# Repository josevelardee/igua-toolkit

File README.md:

# The IGUA toolkit
This is the igua toolkit : )
An open source project to help us get reliable water for everyone, everywhere, anytime.
Done with he support from:

# igua agua, utec ventures, startup perú

#hola!

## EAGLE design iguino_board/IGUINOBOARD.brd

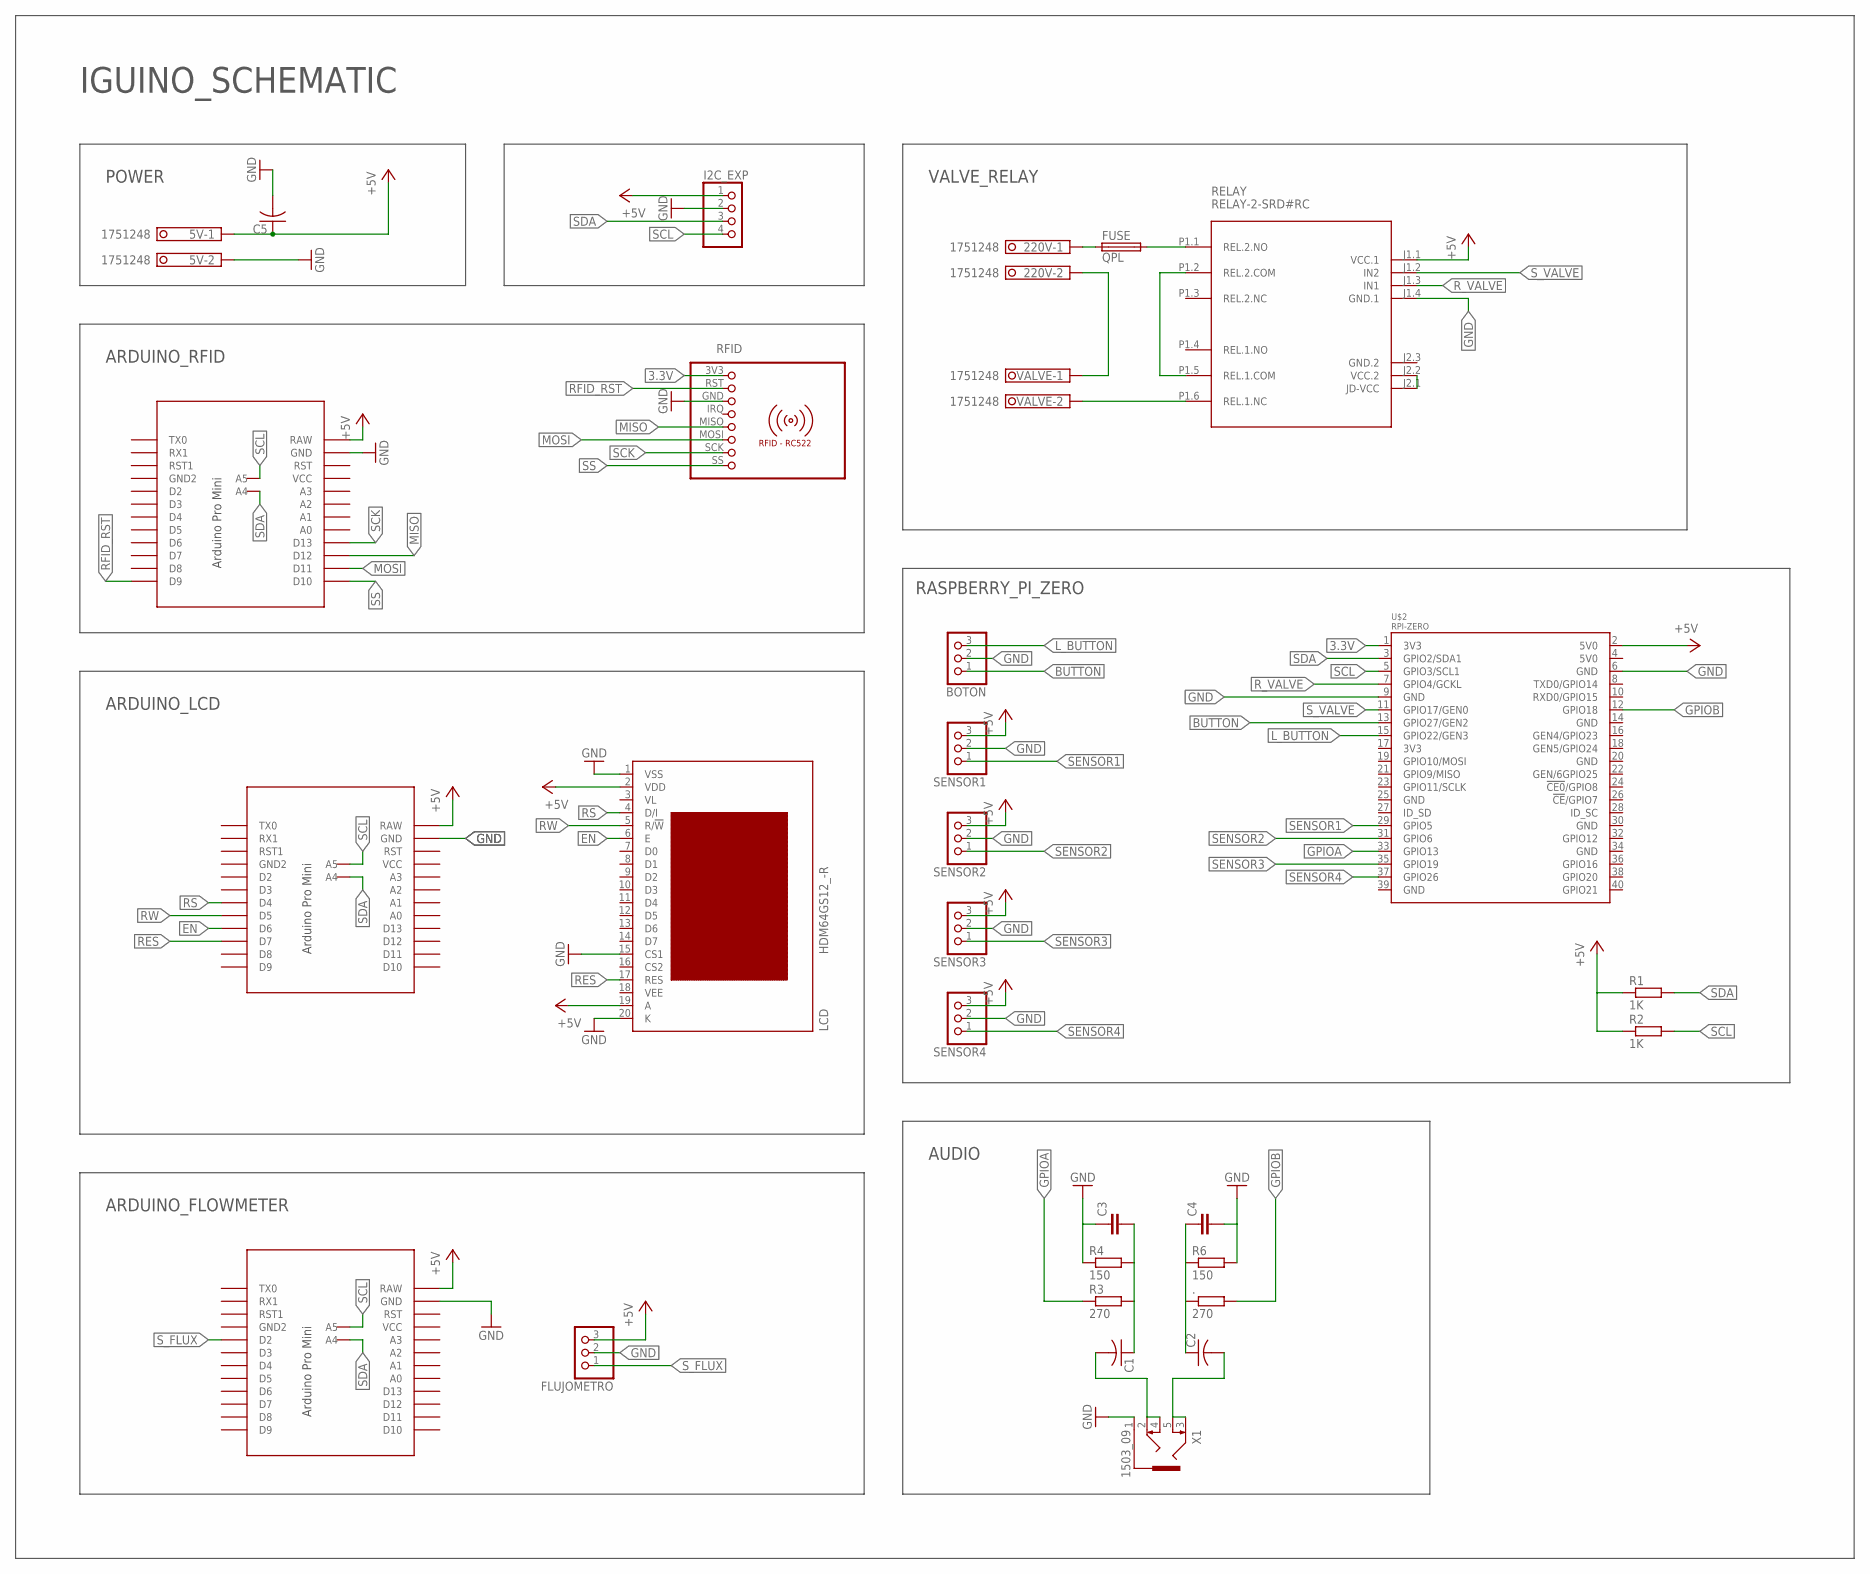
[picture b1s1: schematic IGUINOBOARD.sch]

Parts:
5V, 220V: 1751248
.: 270; 0204/7
BOTON: PINHD-1X3; 1X03
C1, C2, C5: C-US025-024X044; C025-024X044
C3, C4: C-EU025-030X050; C025-030X050
FLUJOMETRO: PINHD-1X3; 1X03
FUSE: QPL
I2C_EXP: PINHD-1X4; 1X04
LCD: HDM64GS12_-R
R1, R2: 1K; 0204/7
R3: 270; 0204/7
R4, R6: 150; 0204/7
RELAY: RELAY-2-SRD#RC
RFID: RFID-RC522
SENSOR1, SENSOR2, SENSOR3, SENSOR4: PINHD-1X3; 1X03
U$1, U$5, U$6: PRO-MINI-2
U$2: RPI-ZERO; RASP_PI_ZERO_BOARD_FULL
VALVE: 1751248
X1: 1503_09

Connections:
3.3V: RFID.3V3 (1), U$2.1 (3V3)
+5V: 5V.1, C5.1, FLUJOMETRO.3, I2C_EXP.1, LCD.2 (VDD), LCD.19 (A), R1.1, R2.1, RELAY.J1.1 (VCC.1), SENSOR1.3, SENSOR2.3, SENSOR3.3, SENSOR4.3, U$1.RAW, U$2.2 (5V0), U$5.RAW, U$6.RAW
BUTTON: BOTON.1, U$2.13 (GPIO27/GEN2)
EN: LCD.6 (E), U$5.D6
GND: 5V.2, BOTON.2, C3.1, C4.2, C5.2, FLUJOMETRO.2, I2C_EXP.2, LCD.1 (VSS), LCD.15 (CS1), LCD.20 (K), R4.1, R6.2, RELAY.J1.4 (GND.1), RFID.GND (3), SENSOR1.2, SENSOR2.2, SENSOR3.2, SENSOR4.2, U$1.GND, U$2.6 (GND), U$2.9 (GND), U$5.GND, U$6.GND, X1.1
GND.2: RELAY.J2.3 (GND.2)
GPIOA: R3.1, U$2.33 (GPIO13)
GPIOB: ..2, U$2.12 (GPIO18)
L_BUTTON: BOTON.3, U$2.15 (GPIO22/GEN3)
MISO: RFID.MISO (5), U$6.D12
MOSI: RFID.MOSI (6), U$6.D11
unnamed: RELAY.P1.6 (REL.1.NC), VALVE.2
unnamed: C1.1, C3.2, R3.2, R4.2
unnamed: ..1, C2.1, C4.1, R6.1
unnamed: C1.2, X1.2, X1.4
unnamed: C2.2, X1.3, X1.5
unnamed: 220V.1, FUSE.1
unnamed: RELAY.P1.2 (REL.2.COM), RELAY.P1.5 (REL.1.COM)
unnamed: FUSE.2, RELAY.P1.1 (REL.2.NO)
unnamed: 220V.2, VALVE.1
unnamed: RELAY.J2.1 (JD-VCC), RELAY.J2.2 (VCC.2)
RES: LCD.17 (RES), U$5.D7
RFID_RST: RFID.RST (2), U$6.D9
RS: LCD.4 (D/I), U$5.D4
RW: LCD.5 (R/!W), U$5.D5
R_VALVE: RELAY.J1.3 (IN1), U$2.7 (GPIO4/GCKL)
SCK: RFID.SCK (7), U$6.D13
SCL: I2C_EXP.4, R2.2, U$1.A5, U$2.5 (GPIO3/SCL1), U$5.A5, U$6.A5
SDA: I2C_EXP.3, R1.2, U$1.A4, U$2.3 (GPIO2/SDA1), U$5.A4, U$6.A4
SENSOR1: SENSOR1.1, U$2.29 (GPIO5)
SENSOR2: SENSOR2.1, U$2.31 (GPIO6)
SENSOR3: SENSOR3.1, U$2.35 (GPIO19)
SENSOR4: SENSOR4.1, U$2.37 (GPIO26)
SS: RFID.SS (8), U$6.D10
S_FLUX: FLUJOMETRO.1, U$1.D2
S_VALVE: RELAY.J1.2 (IN2), U$2.11 (GPIO17/GEN0)

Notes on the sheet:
ARDUINO_FLOWMETER
ARDUINO_LCD
ARDUINO_RFID
POWER
RASPBERRY_PI_ZERO
VALVE_RELAY
AUDIO
IGUINO_SCHEMATIC

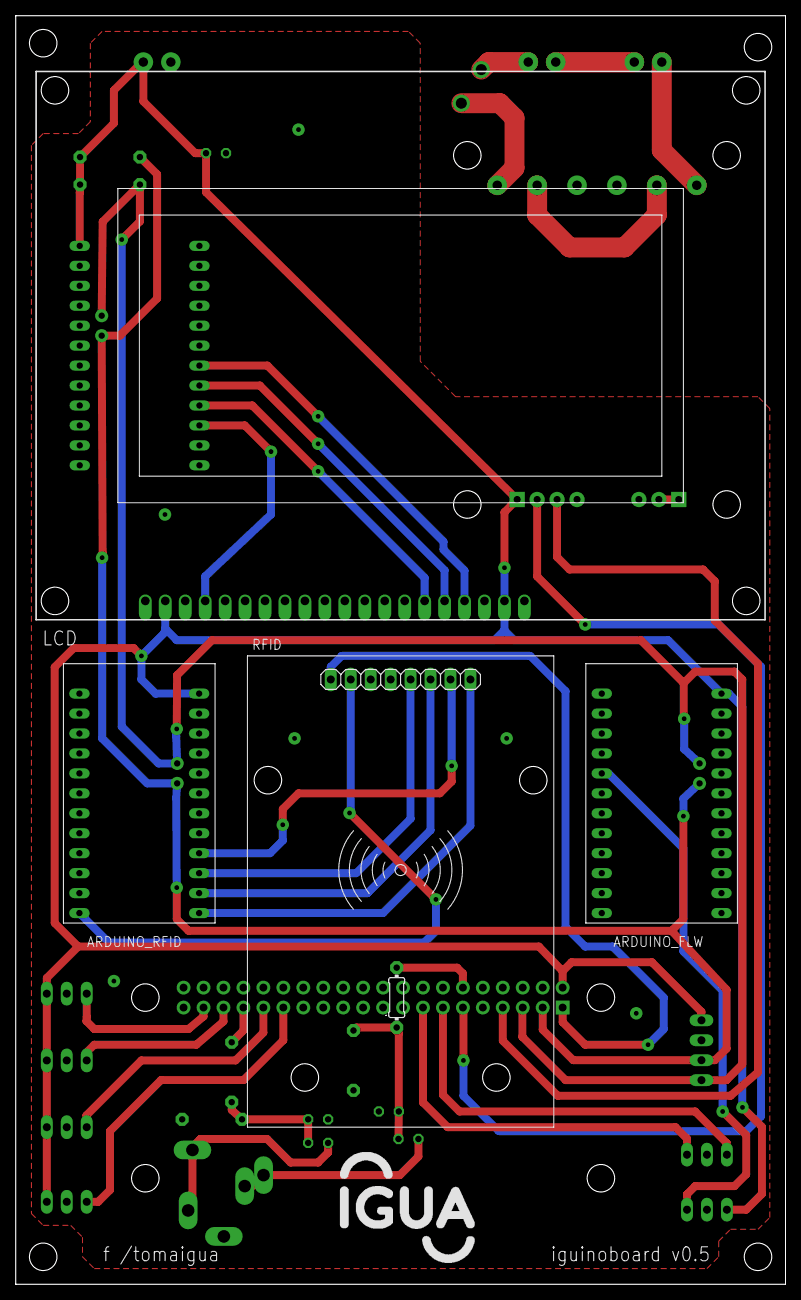
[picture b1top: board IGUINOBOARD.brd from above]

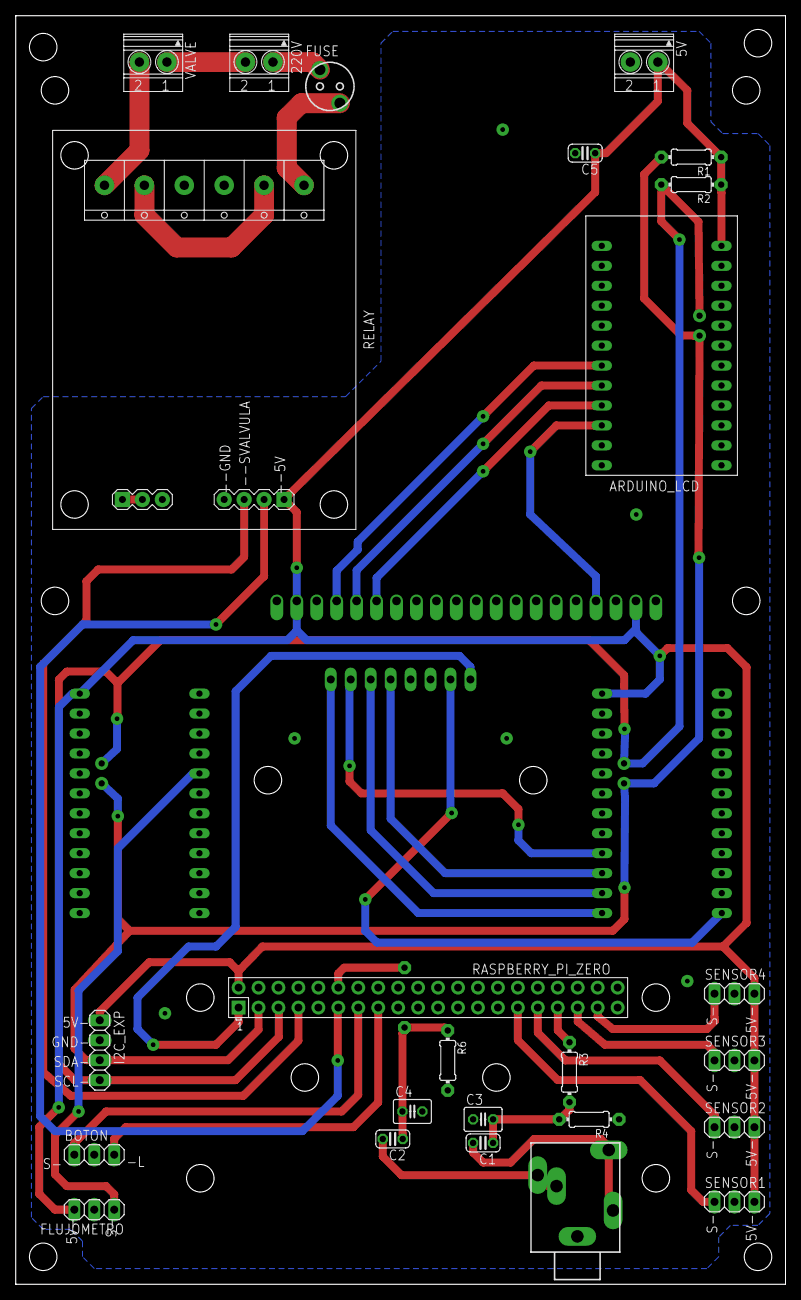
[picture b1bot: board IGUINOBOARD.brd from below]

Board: 2 copper layers, 98.0 x 161.5 mm, 30 parts (25 on the bottom side), 35 nets.

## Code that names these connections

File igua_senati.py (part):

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GPIO.setwarnings(False)

button = 4				# GPIO04, pin nro 07 
valve_relay = 17		# GPIO17, pin nro 11   
button2 = 27			# GPIO27, pin nro 13
spritz_relay = 22		# GPIO22, pin nro 15
coinhibitor_relay = 23	# GPIO23, pin nro 16
UV_relay = 18			# GPIO18, pin nro 12

GPIO.setup(button, GPIO.IN, GPIO.PUD_UP)
GPIO.setup(button2, GPIO.IN, GPIO.PUD_UP)
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
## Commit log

2017-11-09 regresando a lo basico con el flowmeter
2017-11-10 release 1.0
2017-11-10 calibrando
2017-11-10 realease 1.0.1
2017-11-11 fixing the bug
2017-11-14 igua bookmarks
2017-11-22 agregando codigo de Carlos Atahualpa
2017-11-22 Agregando arduino metales pesados
2017-11-22 adaptando el TDS
2017-12-12 re calibrando y simplificando el flujometro
2017-12-12 timeout de coin accepting state
2017-12-12 estabilizando pantalla lcd y rate com flujometro
2017-12-12 uncommenting autostart on default igua lxsession : )
2018-01-05 iniciando integracion igua-senati
2018-01-07 senati ya reporta presiones y tds string
2018-01-25 arduino as dispenser at selvamonos
2018-01-25 selvamonos: sumador y streamer de raspi para surtidores en arduino
2018-01-26 igua selvamonos con tres arduinos y un raspi
2018-01-26 calibrados los tomatodos y escribiendo a la pantalla
2018-01-26 ajustes selvamonos
2018-01-27 sin flojometro pero con excel
2018-02-27 iniciando leanflowmeter ofiselva
2018-02-27 resetter flowmeter
2018-02-28 resetting flowmeter done?
2018-03-03 calibrado el flujometro final final
2018-03-05 release ofiselva
2018-05-02 limpiando codigo
2018-05-07 flowmeter bidirectioinal at toolkit
2018-05-07 asi està quedando lista para regresar a DANNY _ con ozono
2018-05-07 almost back to bodega danny
2018-05-08 ozono periódico en standby
2018-05-08 agregado el ozono
2018-05-08 agradece lo antes posible
2018-05-08 nombre de la maquina,, bodega danny
2018-05-10 tuneando el ozono - ya era mucho
2018-05-16 quitando impresiones en exceso que colgaban el proceso python
2018-05-16 limpiando créditos
2018-05-16 agrandando la letra de los creditos
2018-06-16 migrando a cuentas de igua.devs@gmail.com
2018-06-17 mejorando display parados filas
2018-06-20 agregando keypad
2018-06-25 keypad working w break functions
2018-06-25 little typo fix
2018-06-25 agregando el iguino blocks i2c de jose velarde y el igua toolkit-i2c de jose velarde
2018-06-27 keypad funciona con o sin numlock!
2018-06-27 nicer keypad
2018-06-27 agregando campo de formadepago para stream de carriots
2018-06-29 creando logfile en autostart (lxsession)
2018-07-04 agregando *keypadpasses y comunicando con spreadsheets
2018-07-05 just cleaning up a bit
2018-07-05 borrando basuritas y limpiando el codigo
2018-07-06 generando accounts con drive
2018-07-07 sigo avanzando con los iguapass
2018-07-07 small unvoluntary typo fixed
2018-07-07 little fixes to gspraed exception and more
2018-07-07 retirando el secreto
2018-07-07 cambiando la resolución para VNC, mediante l archivo /boot/config.txt
2018-07-07 accounts listos
2018-07-12 escribiendo a la vez en drive los servings y tambien compactando carriots-makerevent-drive a tres columnas
2018-07-13 mejora la tabla resultante de servings en drive y tambien arregla la desconexion de la autenticacion
2018-07-15 agregando planes 7x1 y 30dias
2018-07-15 vencimiento por plazo a los planes
2018-07-15 mejoras a mensajes de las pantallas iguapass
2018-07-16 arreglando reconexion con drive en escritura de saldos
2018-07-17 fixing typo: crEdito y no crédito
2018-07-18 subiendo v3 de igua-toolkit i2c
2018-07-19 empezando la fusión entre i2c y usb
2018-07-19 empezando2 la fusión entre i2c y usb
2018-07-19 dual pero solo implementado para usb
2018-07-19 fixes a dual, previo a lcd_string
2018-07-20 keypad y gspread ya casi están pulidos. también se abrtrajo todo lo de gspread a una función
2018-07-20 limpiando carpeta
2018-07-20 arreglando bugs en keypad interaction
2018-07-21 empezando el mega merge
2018-07-21 subiendo test.rtf
2018-07-21 aprendiendo a merge
2018-07-21 agregando i2c
2018-07-28 Agragando nuevo LCD
2018-07-30 testeado y ok primera prueba en i2c
2018-07-30 con sonido!
2018-07-30 subiendo soniditos
2018-07-30 agregando sonidos
2018-07-30 something?
2018-07-30 un sonido mas cortito para keypress
2018-07-31 eligiendo los sonidos
2018-08-01 agregando lcd litros y probando rfid
2018-08-01 agregando bloques arduino i2c
2018-08-02 areano boton y led
2018-08-08 corrigiendo bug atrasado en modo usb
2018-08-09 agregando info de como instalar el zte de telefonica
2018-08-20 lcd i2c update
2018-08-25 invirtiendo valvulas para modo i2c
2018-08-29 probando conectarme con erictel, exito
2018-08-29 que se reencienda solo
2018-09-02 detectando flancos y en vias de enclavar
2018-09-03 iguino_board

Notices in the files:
parts and their libraries:
diy-modules: Released under the Creative Commons Attribution 4.0 International License: http://creativecommons.org/licenses/by/4.0
